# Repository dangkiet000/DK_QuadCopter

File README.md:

# DK_QuadCopter
Project quadcopter DIY completely

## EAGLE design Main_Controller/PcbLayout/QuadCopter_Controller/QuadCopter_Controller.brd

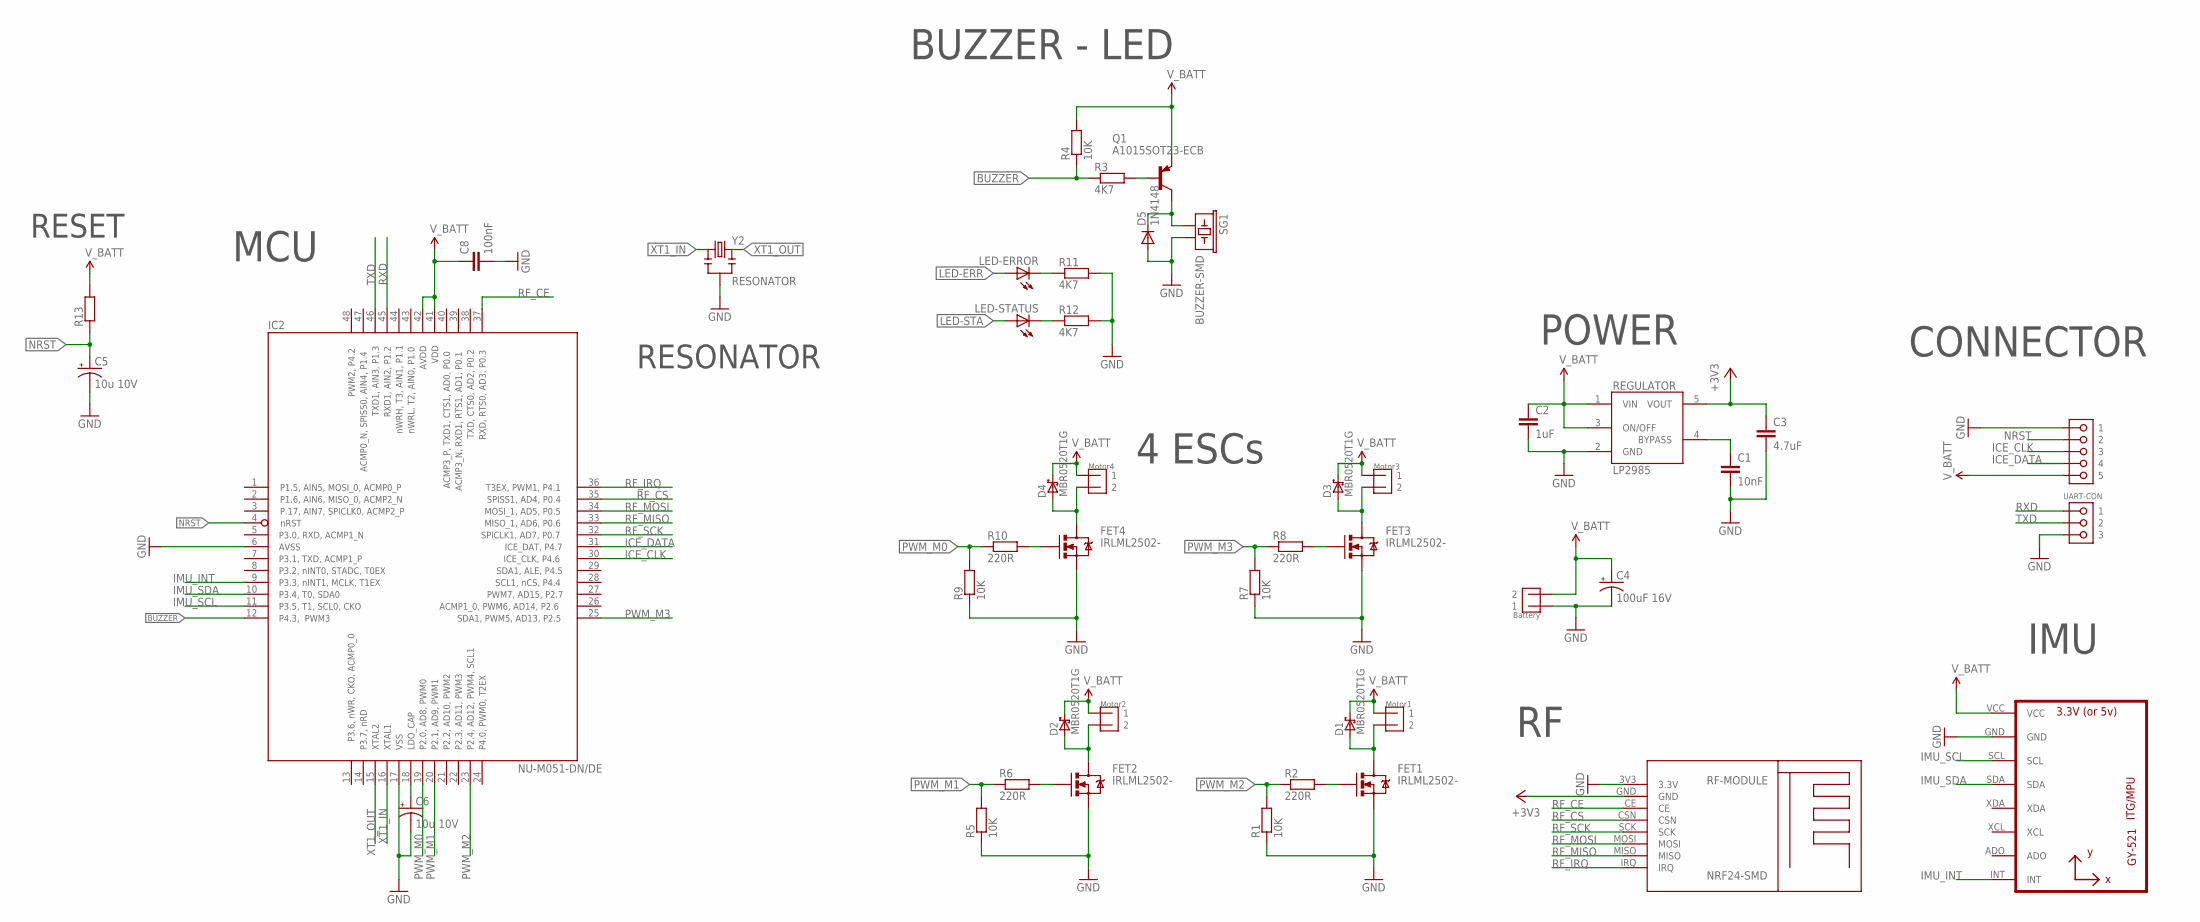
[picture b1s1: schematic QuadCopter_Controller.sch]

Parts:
BATTERY: Battery; WAFER-CON-2P
C1: 10nF; C0603K
C2: 1uF; C0603K
C3: 4.7uF; C0603K
C4: 100uF 16V; PANASONIC_D
C5, C6: 10u 10V; EIA3216
C8: 100nF; C0603K
D1, D2, D3, D4: MBR0520T1G; SOD123
D5: 1N4148; SOD123
FET1, FET2, FET3, FET4: IRLML2502-; SOT-23
IC2: NU-M051-DN/DE; LQFP48
LED-ERROR: LED0805; LED_0805
LED-STATUS: LED0805; LED_0805
MOTOR1: Motor1; WAFER-CON-2P
MOTOR2: Motor2; WAFER-CON-2P
MOTOR3: Motor3; WAFER-CON-2P
MOTOR4: Motor4; WAFER-CON-2P
Q1: A1015SOT23-ECB; SOT23-ECB
R1, R5, R7, R9: 10K; R0603
R2, R6, R8, R10: 220R; R0603
R3, R11, R12: 4K7; R0805
R4: 10K; R0805
R13: RESISTOR-SMDR0603; R0603
REGULATOR: Regulator; SOT25
RF-MODULE: NRF24-SMD
SG1: BUZZER-SMD; BUZZER-CCV-KIT
U1: GY-521MPU6050; GY-521
U$1: ICE_CON; WAFER-CON-5P
U$2: UART-CON; WAFER-CON-3P
Y2: RESONATOR; RESONATOR-SMD

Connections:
+3V3: C3.1, REGULATOR.5 (VOUT), RF-MODULE.GND
BUZZER: IC2.12, R3.1, R4.1
BYPASS: C1.1, REGULATOR.4 (BYPASS)
GND: BATTERY.P$1 (1), C1.2, C2.2, C3.2, C4.-, C5.C (-), C6.C (-), C8.2, D5.A, FET1.2 (S), FET2.2 (S), FET3.2 (S), FET4.2 (S), IC2.6, IC2.17, R1.1, R5.1, R7.1, R9.1, R11.2, R12.2, REGULATOR.2 (GND), RF-MODULE.3V3 (3.3V), SG1.- (2), U1.GND, U$1.P$1 (1), U$2.P$3 (3), Y2.2
ICE_CLK: IC2.30, U$1.P$3 (3)
ICE_DATA: IC2.31, U$1.P$4 (4)
IMU_INT: IC2.9, U1.INT
IMU_SCL: IC2.11, U1.SCL
IMU_SDA: IC2.10, U1.SDA
LED-ERR: LED-ERROR.A
LED-STA: LED-STATUS.A
unnamed: FET1.1 (G), R2.2
unnamed: D5.C, Q1.C, SG1.+ (1)
unnamed: D1.A, FET1.3 (D), MOTOR1.P$2 (2)
unnamed: FET2.1 (G), R6.2
unnamed: D2.A, FET2.3 (D), MOTOR2.P$2 (2)
unnamed: FET3.1 (G), R8.2
unnamed: D3.A, FET3.3 (D), MOTOR3.P$2 (2)
unnamed: Q1.B, R3.2
unnamed: FET4.1 (G), R10.2
unnamed: D4.A, FET4.3 (D), MOTOR4.P$2 (2)
unnamed: LED-STATUS.C, R12.1
unnamed: LED-ERROR.C, R11.1
unnamed: C6.A (+), IC2.18
NRST: C5.A (+), IC2.4, R13.1, U$1.P$2 (2)
PWM_M0: IC2.19, R9.2, R10.1
PWM_M1: IC2.20, R5.2, R6.1
PWM_M2: IC2.23, R1.2, R2.1
PWM_M3: IC2.25, R7.2, R8.1
RF_CE: IC2.37, RF-MODULE.CE
RF_CS: IC2.35, RF-MODULE.CSN
RF_IRQ: IC2.36, RF-MODULE.IRQ
RF_MISO: IC2.33, RF-MODULE.MISO
RF_MOSI: IC2.34, RF-MODULE.MOSI
RF_SCK: IC2.32, RF-MODULE.SCK
RXD: IC2.45, U$2.P$1 (1)
TXD: IC2.46, U$2.P$2 (2)
V_BATT: BATTERY.P$2 (2), C2.1, C4.+, C8.1, D1.C, D2.C, D3.C, D4.C, IC2.41, IC2.42, MOTOR1.P$1 (1), MOTOR2.P$1 (1), MOTOR3.P$1 (1), MOTOR4.P$1 (1), Q1.E, R4.2, R13.2, REGULATOR.1 (VIN), REGULATOR.3 (ON/OFF), U1.VCC, U$1.P$5 (5)
XT1_IN: IC2.16, Y2.1
XT1_OUT: IC2.15, Y2.3

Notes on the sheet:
4 ESCs
IMU
BUZZER - LED
POWER
CONNECTOR
MCU
RESONATOR
RESET

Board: 2 copper layers, 45 parts (0 on the bottom side), 38 nets, no tracks yet.

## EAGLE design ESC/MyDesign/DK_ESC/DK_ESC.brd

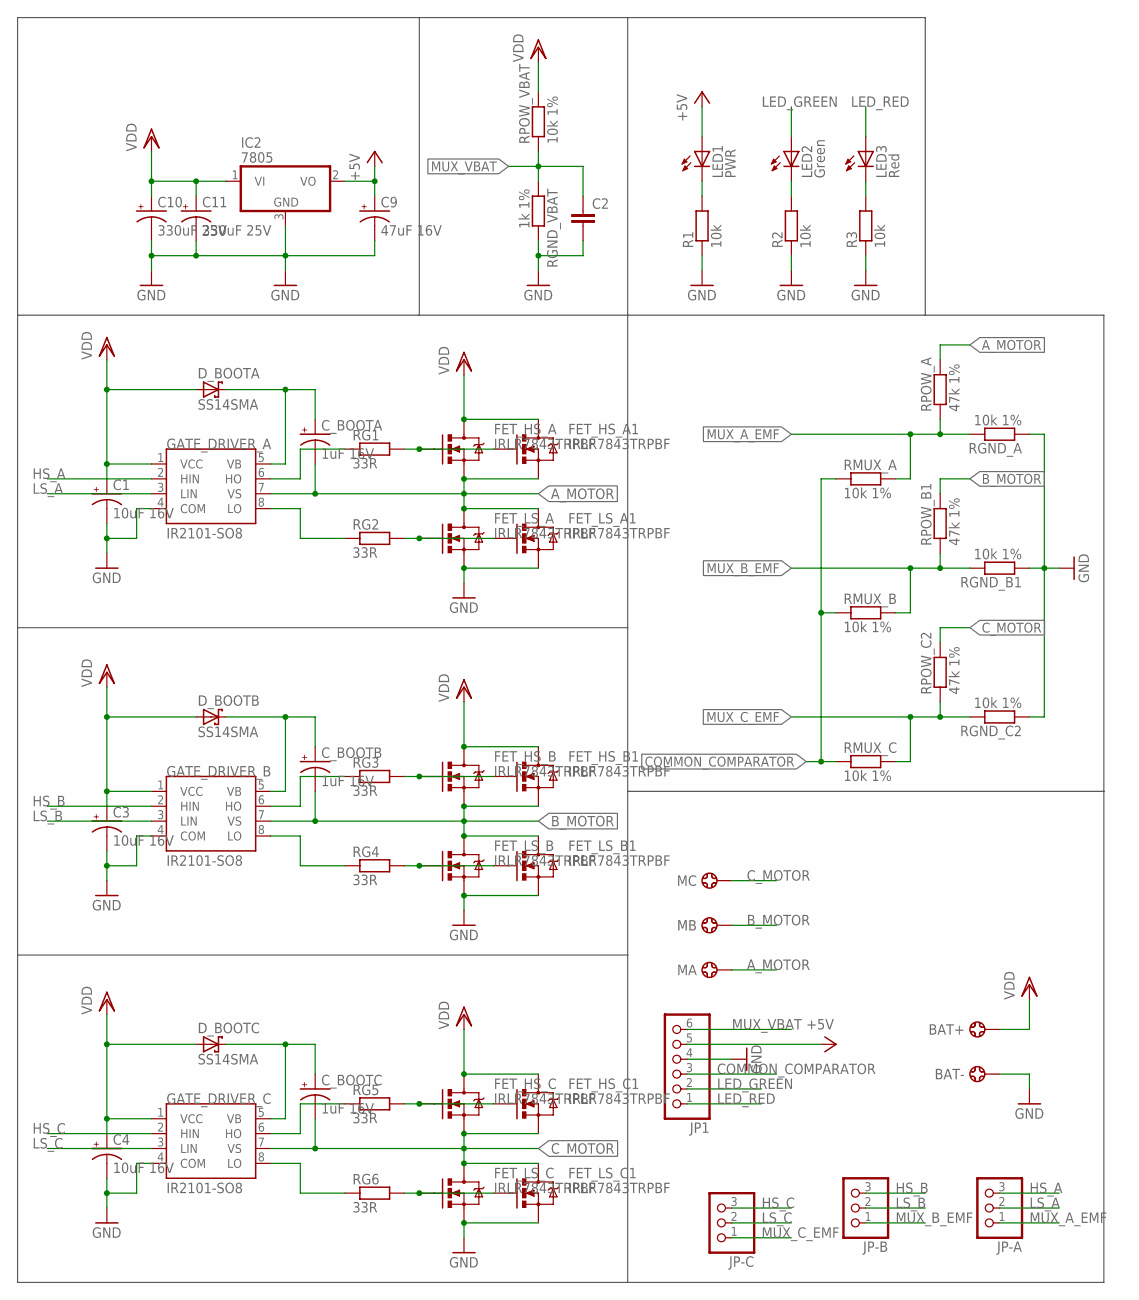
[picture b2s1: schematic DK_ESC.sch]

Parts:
BAT+: 14AWG_PAD-PAD; 14AWG
BAT-: 14AWG_PAD-PAD; 14AWG
C1, C3, C4: 10uF 16V; EIA3216-KIT
C2: C-SMDC0805K; C0805K
C9: 47uF 16V; CT6032
C10, C11: 330uF 25V; CPOL-PTH-330UF-16V
C_BOOTA: 1uF 16V; EIA3216-KIT
C_BOOTB: 1uF 16V; EIA3216-KIT
C_BOOTC: 1uF 16V; EIA3216-KIT
D_BOOTA: SS14SMA; DO214AC
D_BOOTB: SS14SMA; DO214AC
D_BOOTC: SS14SMA; DO214AC
FET_HS_A, FET_HS_A1: IRLR7843TRPBF; TO252
FET_HS_B, FET_HS_B1: IRLR7843TRPBF; TO252
FET_HS_C, FET_HS_C1: IRLR7843TRPBF; TO252
FET_LS_A, FET_LS_A1: IRLR7843TRPBF; TO252
FET_LS_B, FET_LS_B1: IRLR7843TRPBF; TO252
FET_LS_C, FET_LS_C1: IRLR7843TRPBF; TO252
GATE_DRIVER_A: IR2101-SO8; SO08
GATE_DRIVER_B: IR2101-SO8; SO08
GATE_DRIVER_C: IR2101-SO8; SO08
IC2: 7805; TO252
JP1: PINHD-1X6; 1X06
JP-A: PINHD-1X3; 1X03
JP-B: PINHD-1X3; 1X03
JP-C: PINHD-1X3; 1X03
LED1: PWR; LED_0805
LED2: Green; LED_0805
LED3: Red; LED_0805
MA: 14AWG_PAD-PAD; 14AWG
MB: 14AWG_PAD-PAD; 14AWG
MC: 14AWG_PAD-PAD; 14AWG
R1, R2, R3: 10k; R0805
RG1, RG2, RG3, RG4, RG5, RG6: 33R; R0603
RGND_A: 10k 1%; R0805
RGND_B1: 10k 1%; R0805
RGND_C2: 10k 1%; R0805
RGND_VBAT: 1k 1%; R0805
RMUX_A: 10k 1%; R0805
RMUX_B: 10k 1%; R0805
RMUX_C: 10k 1%; R0805
RPOW_A: 47k 1%; R0603
RPOW_B1: 47k 1%; R0603
RPOW_C2: 47k 1%; R0603
RPOW_VBAT: 10k 1%; R0805

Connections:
+5V: C9.+, IC2.2 (VO), JP1.5, LED1.A
A_MOTOR: C_BOOTA.C (-), FET_HS_A.3 (S), FET_HS_A1.3 (S), FET_LS_A.2 (D), FET_LS_A1.2 (D), GATE_DRIVER_A.7 (VS), MA.1, RPOW_A.2
B_MOTOR: C_BOOTB.C (-), FET_HS_B.3 (S), FET_HS_B1.3 (S), FET_LS_B.2 (D), FET_LS_B1.2 (D), GATE_DRIVER_B.7 (VS), MB.1, RPOW_B1.2
COMMON_COMPARATOR: JP1.3, RMUX_A.1, RMUX_B.1, RMUX_C.1
C_MOTOR: C_BOOTC.C (-), FET_HS_C.3 (S), FET_HS_C1.3 (S), FET_LS_C.2 (D), FET_LS_C1.2 (D), GATE_DRIVER_C.7 (VS), MC.1, RPOW_C2.2
GND: BAT-.1, C1.C (-), C2.2, C3.C (-), C4.C (-), C9.-, C10.-, C11.-, FET_LS_A.3 (S), FET_LS_A1.3 (S), FET_LS_B.3 (S), FET_LS_B1.3 (S), FET_LS_C.3 (S), FET_LS_C1.3 (S), GATE_DRIVER_A.4 (COM), GATE_DRIVER_B.4 (COM), GATE_DRIVER_C.4 (COM), IC2.3 (GND), JP1.4, R1.1, R2.1, R3.1, RGND_A.1, RGND_B1.1, RGND_C2.1, RGND_VBAT.2
HS_A: GATE_DRIVER_A.2 (HIN), JP-A.3
HS_B: GATE_DRIVER_B.2 (HIN), JP-B.3
HS_C: GATE_DRIVER_C.2 (HIN), JP-C.3
LED_GREEN: JP1.2, LED2.A
LED_RED: JP1.1, LED3.A
LS_A: GATE_DRIVER_A.3 (LIN), JP-A.2
LS_B: GATE_DRIVER_B.3 (LIN), JP-B.2
LS_C: GATE_DRIVER_C.3 (LIN), JP-C.2
MUX_A_EMF: JP-A.1, RGND_A.2, RMUX_A.2, RPOW_A.1
MUX_B_EMF: JP-B.1, RGND_B1.2, RMUX_B.2, RPOW_B1.1
MUX_C_EMF: JP-C.1, RGND_C2.2, RMUX_C.2, RPOW_C2.1
MUX_VBAT: C2.1, JP1.6, RGND_VBAT.1, RPOW_VBAT.1
unnamed: FET_LS_A.1 (G), FET_LS_A1.1 (G), RG2.2
unnamed: FET_HS_A.1 (G), FET_HS_A1.1 (G), RG1.2
unnamed: FET_LS_B.1 (G), FET_LS_B1.1 (G), RG4.2
unnamed: GATE_DRIVER_A.6 (HO), RG1.1
unnamed: GATE_DRIVER_A.8 (LO), RG2.1
unnamed: FET_HS_B.1 (G), FET_HS_B1.1 (G), RG3.2
unnamed: GATE_DRIVER_B.6 (HO), RG3.1
unnamed: GATE_DRIVER_B.8 (LO), RG4.1
unnamed: FET_LS_C.1 (G), FET_LS_C1.1 (G), RG6.2
unnamed: FET_HS_C.1 (G), FET_HS_C1.1 (G), RG5.2
unnamed: GATE_DRIVER_C.6 (HO), RG5.1
unnamed: GATE_DRIVER_C.8 (LO), RG6.1
unnamed: LED1.C, R1.2
unnamed: LED2.C, R2.2
unnamed: LED3.C, R3.2
VB: C_BOOTA.A (+), C_BOOTB.A (+), C_BOOTC.A (+), D_BOOTA.C, D_BOOTB.C, D_BOOTC.C, GATE_DRIVER_A.5 (VB), GATE_DRIVER_B.5 (VB), GATE_DRIVER_C.5 (VB)
VDD: BAT+.1, C1.A (+), C3.A (+), C4.A (+), C10.+, C11.+, D_BOOTA.A, D_BOOTB.A, D_BOOTC.A, FET_HS_A.2 (D), FET_HS_A1.2 (D), FET_HS_B.2 (D), FET_HS_B1.2 (D), FET_HS_C.2 (D), FET_HS_C1.2 (D), GATE_DRIVER_A.1 (VCC), GATE_DRIVER_B.1 (VCC), GATE_DRIVER_C.1 (VCC), IC2.1 (VI), RPOW_VBAT.2

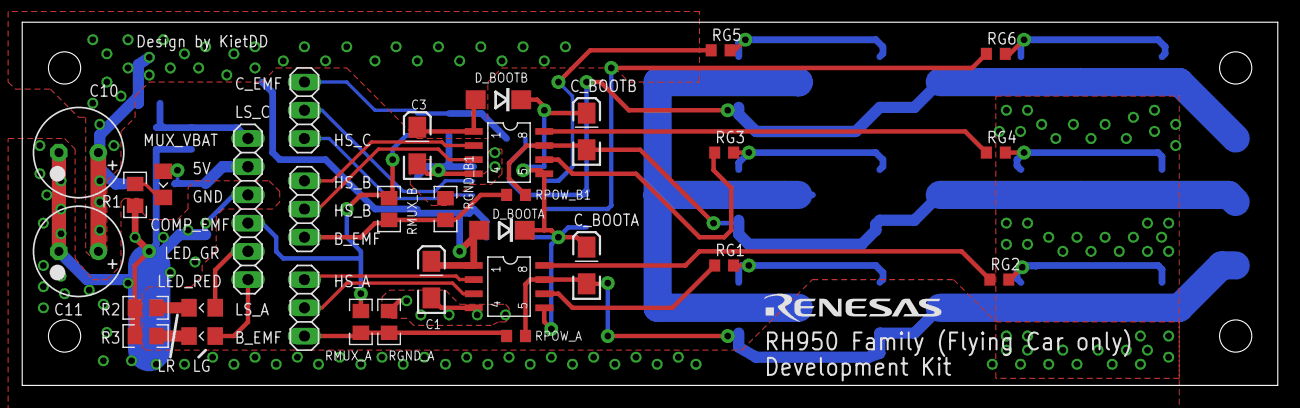
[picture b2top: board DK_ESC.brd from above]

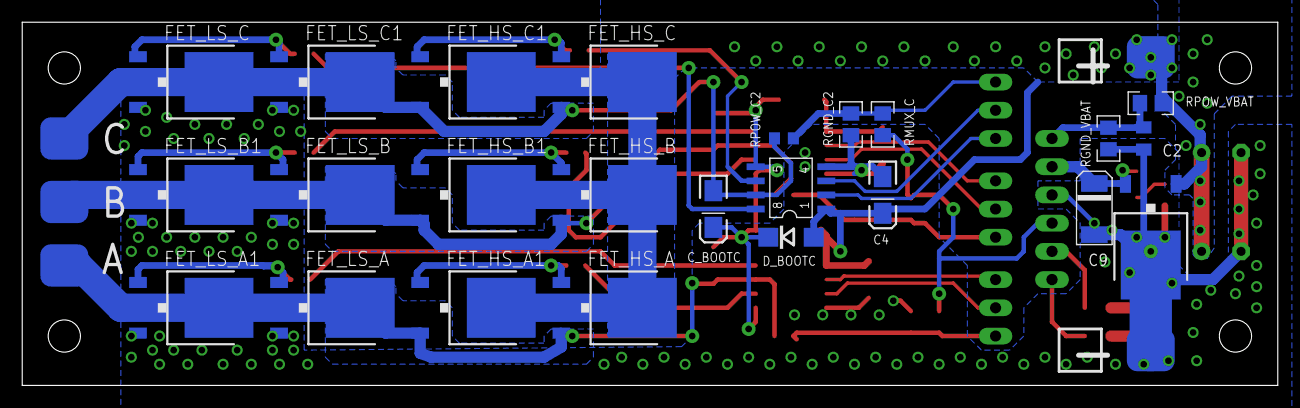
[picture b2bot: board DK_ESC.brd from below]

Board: 2 copper layers, 113.0 x 32.7 mm, 62 parts (29 on the bottom side), 35 nets.

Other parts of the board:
U$2: RENESAS

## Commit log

2017-03-02 [ESC] Init version
2017-03-05 Init my design ESC
2017-03-09 ESC Design: include MCU
2017-03-11 Update layout ESC: test version
2017-03-14 Add Datasheet mosfet and update layout test ESC
2017-03-15 Finish layout test ESC
2017-03-18 Update logo renesas
2017-03-22 Add IMU folder
2017-03-25 Generate Gerber
2017-04-01 Test PS2 Ok!
2017-04-01 Fix error byte5: when E when C
2017-04-02 Test PS2 use SPI Hardware
2017-04-07 Fix error PS2_Data[3] 0xFE by connect R-pullup open-collector PS2 pins
2017-04-09 Create PS2 Dang Kiet library
    Test function Enter PS2 config mode is OK
2017-04-09 Update Exit PS2 config mode
2017-04-10 Add function: PS2_SetMode and PS2_GetMode
2017-04-10 Update: verify by PS2_GetMode
2017-04-10 Fix: print outdata is wrong (8B). Add Ps2_EnableVibration
2017-04-10 Update Limitation
2017-04-11 Add PS2_Read function
2017-04-12 Update PS2_SetMode
    default this function will set SWITCH_MODE_USER:
    Allow user switch mode by push Analog button on gamepad
2017-04-12 Change LaaDataOut to Global variable
    LaaDataOut to PS2_GaaTXData
2017-04-12 Add LEDERROR
2017-07-15 Lau roi moi lam tiep
2017-09-12 Add project IAR Porting Nuvoton to Arduino
2017-09-15 attachInterrupt is OK
2017-09-16 analogWrite function
2017-09-21 Revert "analogWrite function"
    This reverts commit 5b0e0b74105031a6c071572a7f8d95f5cfb4715a.
2017-09-21 Revert "Revert "analogWrite function""
    This reverts commit 2a603a4ba6bf5b1ab145676bf436fa145a98ddc3.
2017-09-23 Fix error overload function has linkage C
2017-09-23 Serial function
2017-09-24 Serial.read() is OK!
2017-09-24 Re-struct folder arduino cores
2017-09-27 Test: HardwareTimer library is OK. Porting Tone
2017-10-03 analogReadVcc and analogRead
2017-11-23 test
    dsa
2019-01-07 Add CJMCU hardware

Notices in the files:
parts and their libraries:
GateDriver: Copyright & License
This library is licensed under the General Public License, Version 2.
More Information about the General Public License is available at http://www.gnu.org/copyleft/gpl.html.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
